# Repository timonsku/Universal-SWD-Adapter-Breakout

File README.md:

# Universal-SWD-Adapter-Breakout

A simple PCB to adapt between common SWD connector variations.
- 20pin 0.1" Cortex SWD connector (as found on the big J-Link's)
- 10pin 0.1" Cortex SWD connector (as found on ST-Link)
- 10pin 0.05" Cortex SWD connector (as found on J-Link Mini and many targets) 
- Named 0.1" pin header row for all 6 main signals
- 6pin 0.1" TC2030-IDC footprint (compact "SWD-Adapter" only) 

There are two variants, one compact version and an expanded version that add an RJ12 connector intended to be used with the TC2030-MCP-NL Tag Connect cables which are used on Microchip programmers and are often the cheapest and easiest to buy Tag Connect cable from distributors. This variant is also useful for having some solder on pads for hard wiring an SWD connection to a device.

BOM
----

- Molex 95501-6669 (RJ12)
- Samtec FTSH-105-01-L-DV-K-TR (2x5 pin 1.27mm SMT shrouded). Cheaper here on AliExpress: https://s.click.aliexpress.com/e/_DmALpMt
- Molex 90130-1110 (2x5 2.54mm PTH Shrouded)
- Molex 90130-1120 (2x10 2.54mm PTH Shrouded)

Various distributor PNs the RJ12 tag connect cable:

NL version:
- 579-TC2030-MCP-NL 

With hooks:
- 733-53025-851
- 579-TC2030-MCP

For DigiKey:
- TC2030-MCP-NLTC-ND
- TC2030-MCPTC-ND

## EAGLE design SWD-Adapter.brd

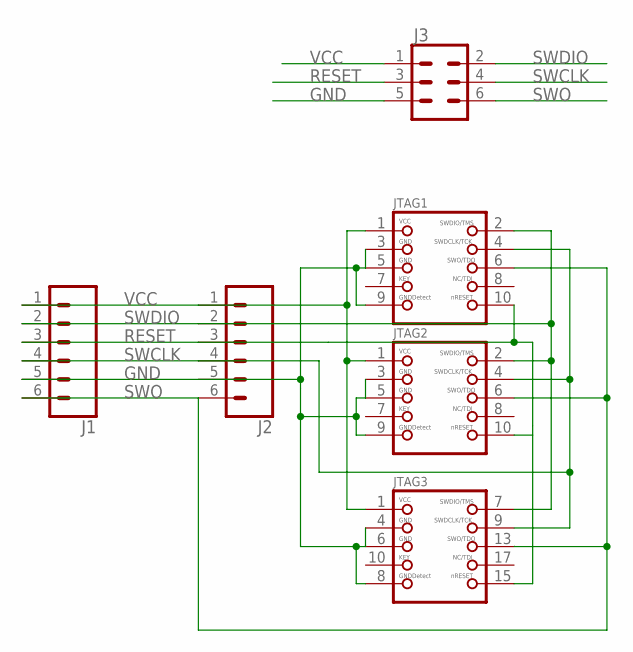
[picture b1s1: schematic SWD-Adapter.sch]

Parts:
J1, J2: CONN_06SILK_FEMALE_PTH; 1X06
J3: CONN_03X2NO_SILK; 2X3-NS
JTAG1: JTAG-CORTEXM3; 2X05_1.27MM_SMT
JTAG2: JTAG-CORTEXM3MOLEX; CORTEXM3_SWD10_MOLEX
JTAG3: JTAG-CORTEXM3MOLEX20; JTAG-ARM

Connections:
GND: J1.5, J2.5, J3.5, JTAG1.3, JTAG1.5, JTAG1.9, JTAG2.3, JTAG2.5, JTAG2.9, JTAG3.4 (3), JTAG3.6 (5), JTAG3.8 (9)
RESET: J1.3, J2.3, J3.3, JTAG1.10, JTAG2.10, JTAG3.15 (10)
SWCLK: J1.4, J2.4, J3.4, JTAG1.4, JTAG2.4, JTAG3.9 (4)
SWDIO: J1.2, J2.2, J3.2, JTAG1.2, JTAG2.2, JTAG3.7 (2)
SWO: J1.6, J2.6, J3.6, JTAG1.6, JTAG2.6, JTAG3.13 (6)
VCC: J1.1, J2.1, J3.1, JTAG1.1, JTAG2.1, JTAG3.1

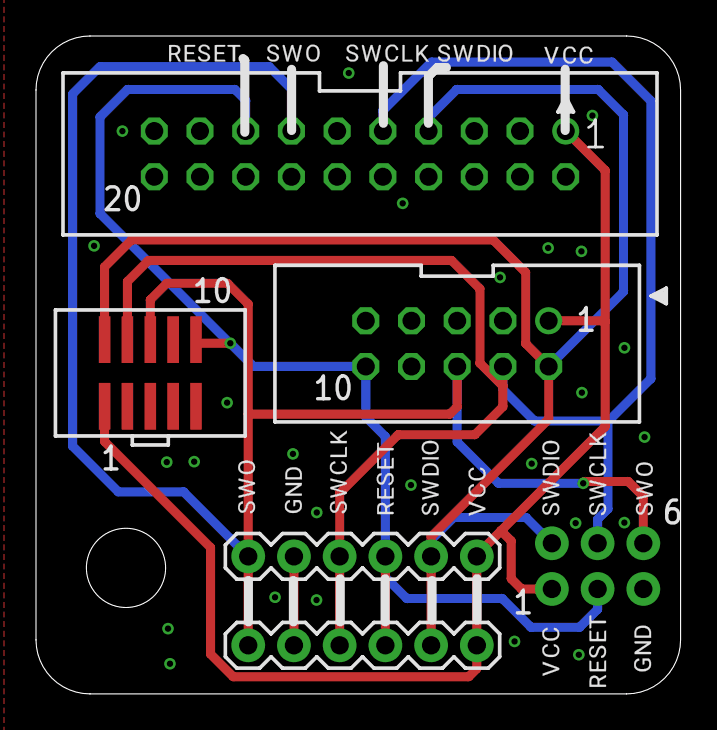
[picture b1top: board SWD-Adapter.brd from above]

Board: 2 copper layers, 35.8 x 36.5 mm, 23 parts (0 on the bottom side), 6 nets.

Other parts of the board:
U$1, U$7, U$12: SWO0
U$2, U$15: GND0
U$3, U$11, U$16: SWCLK0
U$4, U$9, U$13: RESET0
U$5, U$8, U$17: SWDIO0
U$6, U$10, U$14: VCC0

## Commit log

2024-11-20 add compact variant
2025-02-21 add 6pin TC2030 pinout to SWD-Adapter variant
2025-02-21 update RJ12 variant with 6p connector
2025-02-22 update board file

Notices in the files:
parts and their libraries:
SparkFun-Connectors: Licensing: Creative Commons ShareAlike 4.0 International - https://creativecommons.org/licenses/by-sa/4.0
microbuilder: This work is placed in the public domain, and may be freely used for commercial and non-commercial work with the following conditions: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
